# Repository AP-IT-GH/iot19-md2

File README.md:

# Internet of Things - Medical delivery

## Groepsleden

Jarno Cools - Project Manager, Documentating and all-round  
Imad El-Azzouzi - PCB designer, Front-end Programmer and Professional Email Sender to Mr. Luyts         
Oussama Es-Salhi - Back-end Programmer / Systems integrator  
Cristian Baba - Front-end programmer / system testing and programming

## Documentatie

[Medical Delivery Analyse](/doc/analyse.md)

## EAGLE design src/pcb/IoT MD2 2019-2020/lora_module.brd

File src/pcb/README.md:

# PCBs

## MCU module

## LoRa module

## GPS module

## Humidity sensor

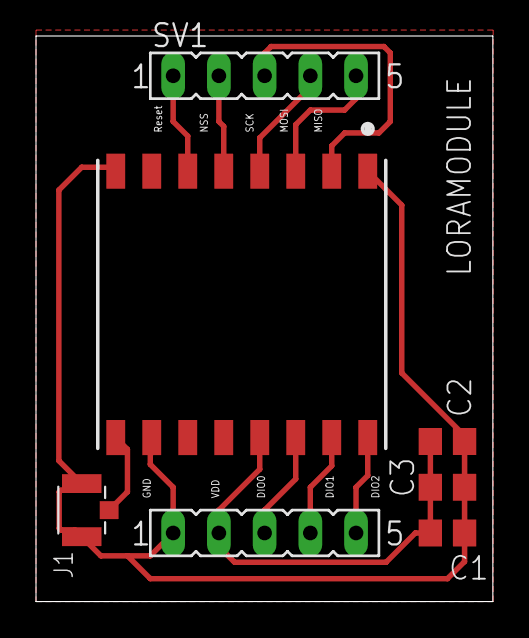
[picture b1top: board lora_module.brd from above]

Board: 2 copper layers, 25.4 x 31.4 mm, 7 parts (0 on the bottom side), 11 nets.

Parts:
C1: 1uF; C0805
C2: 10uF; C0805
C3: 100nF; C0805
J1: U.FL-R-SMT-1(10); HRS_U.FL-R-SMT-1(10)
LORAMODULE: RFM95W-868S2; XCVR_RFM95W-868S2
SV1, SV2: FE05-1

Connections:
DIO0: LORAMODULE.14, SV2.3
DIO1: LORAMODULE.15, SV2.4
DIO2: LORAMODULE.16, SV2.5
GND: C1.2, C2.2, C3.2, J1.1, J1.3, LORAMODULE.1, LORAMODULE.8, LORAMODULE.10, SV2.1
MISO: LORAMODULE.2, SV1.3
MOSI: LORAMODULE.3, SV1.5
unnamed: J1.2, LORAMODULE.9
NSS: LORAMODULE.5, SV1.2
RESET_LORA: LORAMODULE.6, SV1.1
SCK: LORAMODULE.4, SV1.4
VDD: C1.1, C2.1, C3.1, LORAMODULE.13, SV2.2

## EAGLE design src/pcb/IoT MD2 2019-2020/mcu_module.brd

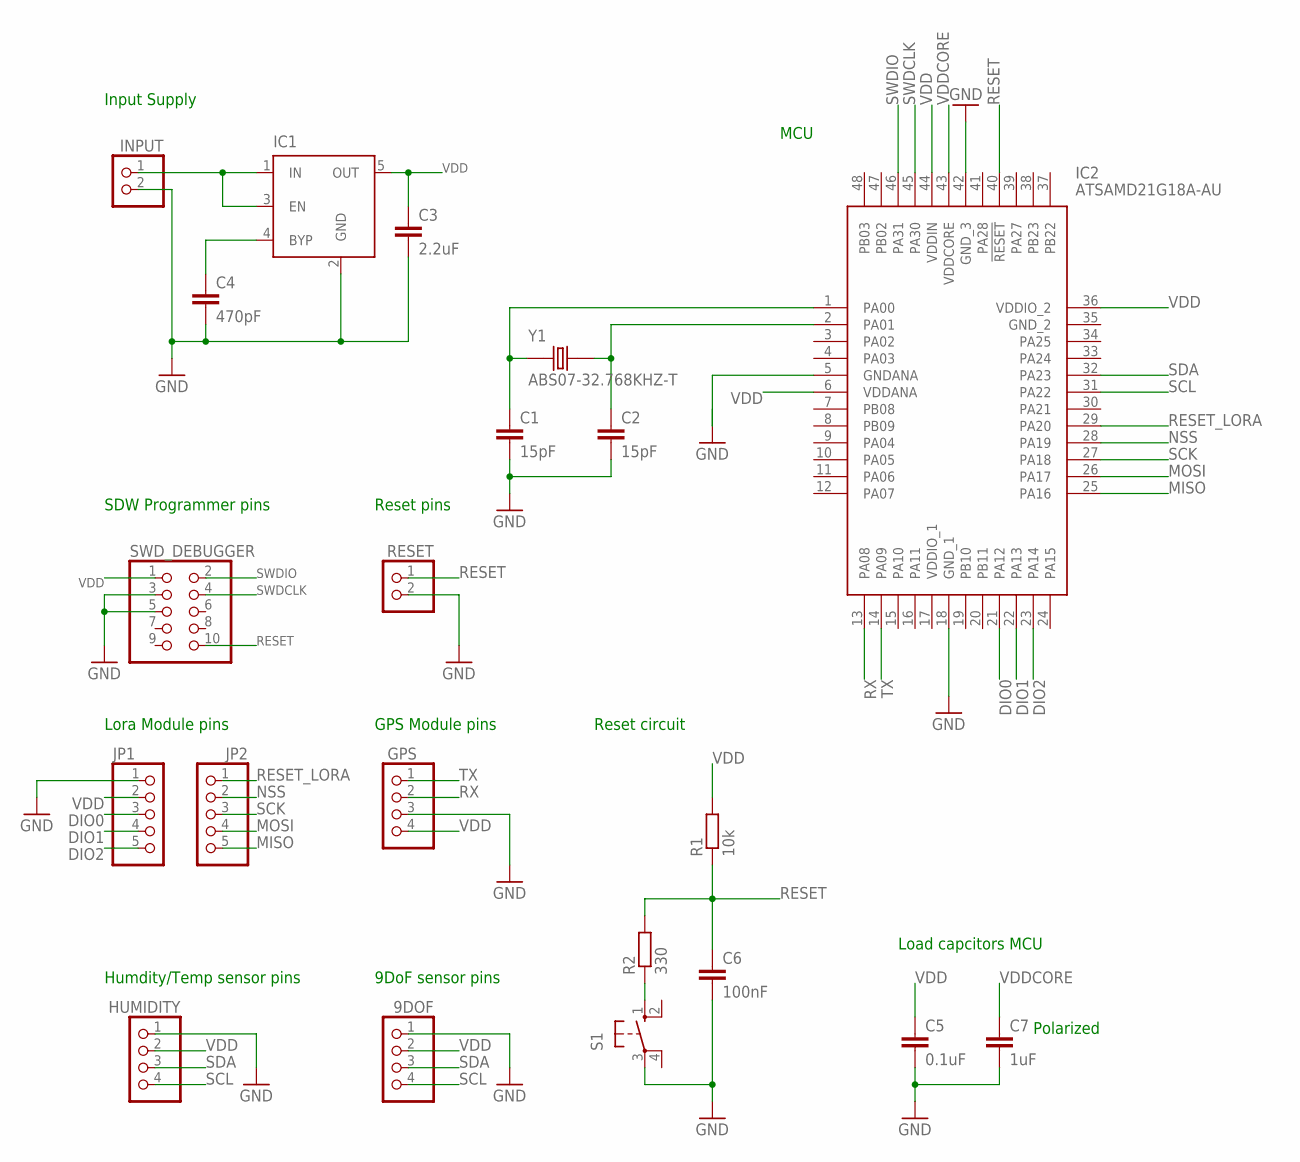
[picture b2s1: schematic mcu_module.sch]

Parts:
9DOF: PINHD-1X4; 1X04
C1, C2: 15pF; C0805
C3: 2.2uF; C0805
C4: 470pF; C0805
C5: 0.1uF; C0805
C6: 100nF; C0805
C7: 1uF; C0805
GPS: PINHD-1X4; 1X04
HUMIDITY: PINHD-1X4; 1X04
IC1: MIC5219XX; SOT23-5
IC2: ATSAMD21G18A-AU; QFP50P900X900X120-48N
INPUT: PINHD-1X2; 1X02
JP1, JP2: PINHD-1X5; 1X05
R1: 10k; R0805
R2: 330; R0805
RESET: PINHD-1X2; 1X02
S1: 10-XX; B3F-10XX
SWD_DEBUGGER: PINHD-2X5; 2X05
Y1: ABS07-32.768KHZ-T; XTAL_ABS07-32.768KHZ-T

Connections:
BYP: C4.1, IC1.4 (BYP)
DIO0: IC2.21 (PA12), JP1.3
DIO1: IC2.22 (PA13), JP1.4
DIO2: IC2.23 (PA14), JP1.5
GND: 9DOF.1, C1.2, C2.2, C3.2, C4.2, C5.2, C6.2, C7.2, GPS.3, HUMIDITY.1, IC1.2 (GND), IC2.5 (GNDANA), IC2.18 (GND_1), IC2.42 (GND_3), INPUT.2, JP1.1, RESET.2, S1.3, SWD_DEBUGGER.3, SWD_DEBUGGER.5
INPUT: IC1.1 (IN), IC1.3 (EN), INPUT.1
MISO: IC2.25 (PA16), JP2.5
MOSI: IC2.26 (PA17), JP2.4
unnamed: C1.1, IC2.1 (PA00), Y1.1
unnamed: C2.1, IC2.2 (PA01), Y1.2
unnamed: R2.1, S1.1 (S)
NSS: IC2.28 (PA19), JP2.2
RESET: C6.1, IC2.40 (!RESET), R1.1, R2.2, RESET.1, SWD_DEBUGGER.10
RESET_LORA: IC2.29 (PA20), JP2.1
RX: GPS.2, IC2.13 (PA08)
SCK: IC2.27 (PA18), JP2.3
SCL: 9DOF.4, HUMIDITY.4, IC2.31 (PA22)
SDA: 9DOF.3, HUMIDITY.3, IC2.32 (PA23)
SWDCLK: IC2.45 (PA30), SWD_DEBUGGER.4
SWDIO: IC2.46 (PA31), SWD_DEBUGGER.2
TX: GPS.1, IC2.14 (PA09)
VDD: 9DOF.2, C3.1, C5.1, GPS.4, HUMIDITY.2, IC1.5 (OUT), IC2.6 (VDDANA), IC2.36 (VDDIO_2), IC2.44 (VDDIN), JP1.2, R1.2, SWD_DEBUGGER.1
VDDCORE: C7.1, IC2.43 (VDDCORE)

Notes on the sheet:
Input Supply
SDW Programmer pins
Reset pins
Lora Module pins
Load capcitors MCU
Reset circuit
GPS Module pins
Humdity/Temp sensor pins
9DoF sensor pins
MCU
Polarized

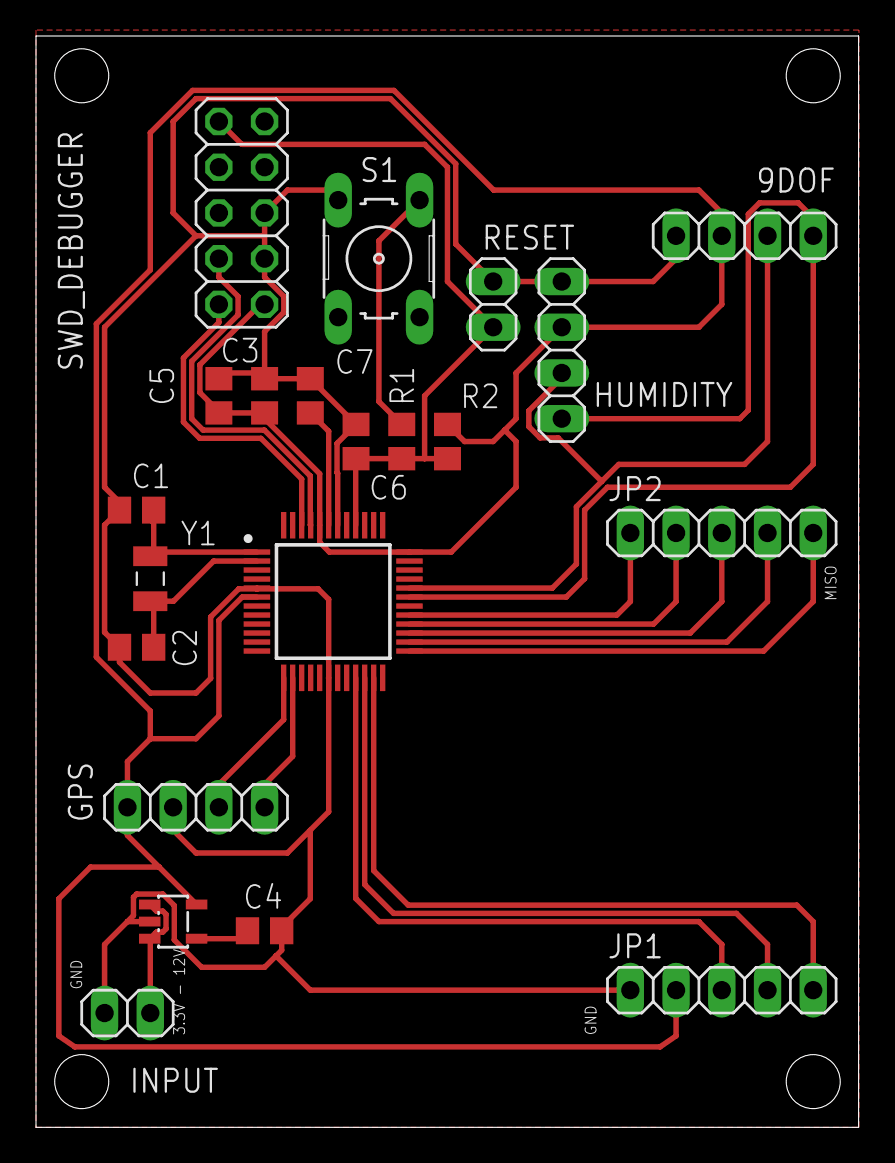
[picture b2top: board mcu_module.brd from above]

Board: 2 copper layers, 45.7 x 60.6 mm, 21 parts (0 on the bottom side), 23 nets.

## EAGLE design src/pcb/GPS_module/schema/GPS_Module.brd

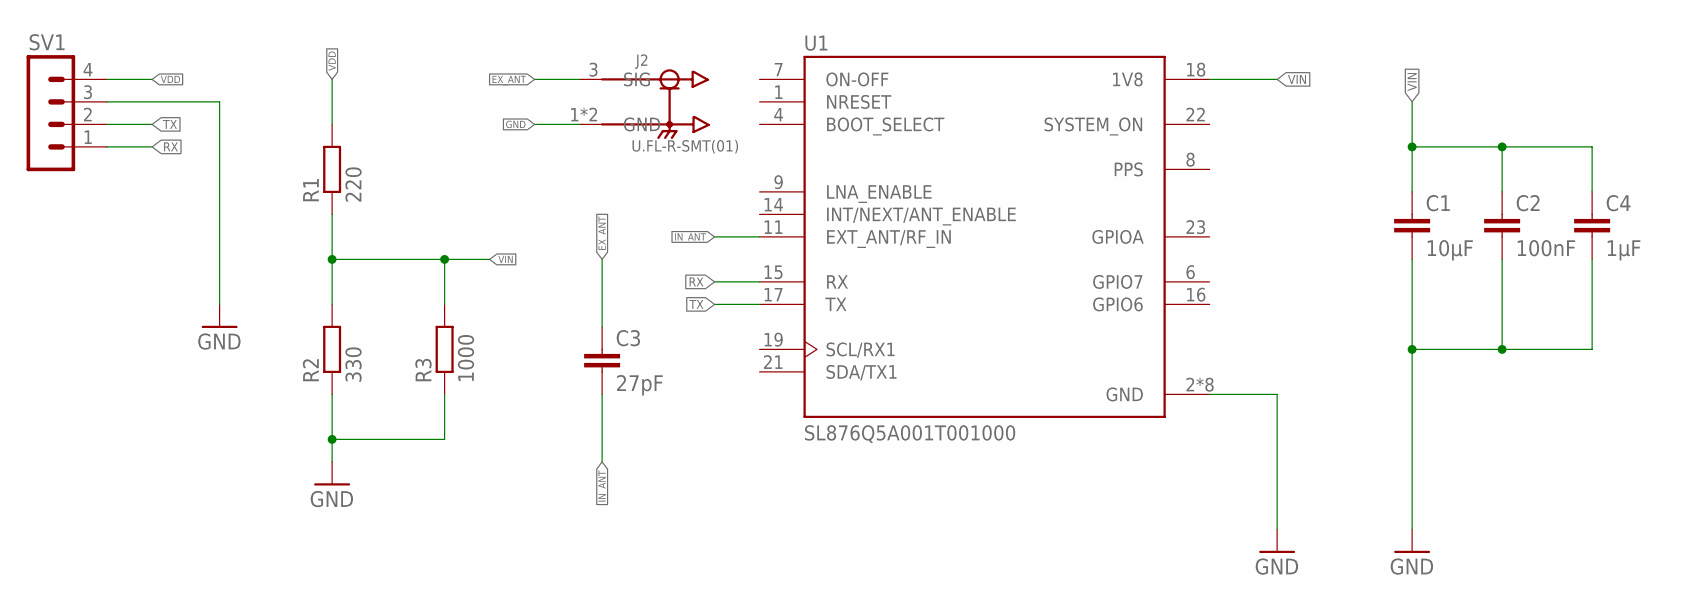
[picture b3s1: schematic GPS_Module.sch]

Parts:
C1: 10µF; C0805
C2: 100nF; C0805
C3: 27pF; C0805
C4: 1µF; C0805
J2: U.FL-R-SMT(01); HRS_U.FL-R-SMT(01)
R1: 220; R0402
R2: 330; R0402
R3: 1000; R0402
SV1: MA04-1
U1: SL876Q5A001T001000; XCVR_SL876Q5A001T001000

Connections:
EX_ANT: C3.1, J2.3 (SIG)
GND: C1.2, C2.2, C4.2, J2.1 (GND), J2.2 (GND), R2.1, R3.1, SV1.3, U1.2 (GND), U1.3 (GND), U1.5 (GND), U1.10 (GND), U1.12 (GND), U1.13 (GND), U1.20 (GND), U1.24 (GND)
IN_ANT: C3.2, U1.11 (EXT_ANT/RF_IN)
RX: SV1.1, U1.15 (RX)
TX: SV1.2, U1.17 (TX)
VDD: R1.2, SV1.4
VIN: C1.1, C2.1, C4.1, R1.1, R2.2, R3.2, U1.18 (1V8)

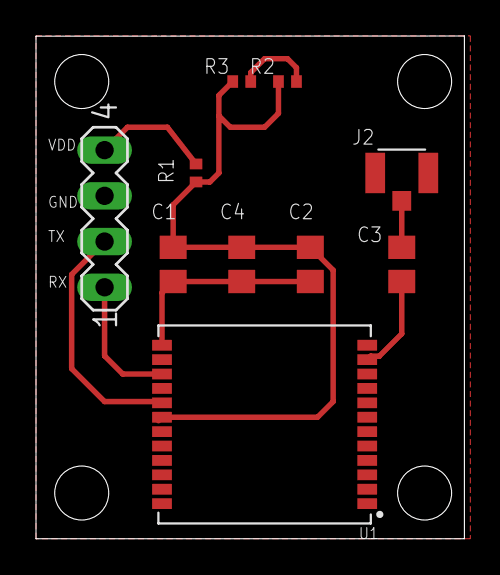
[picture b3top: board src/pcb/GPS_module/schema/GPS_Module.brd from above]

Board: 2 copper layers, 23.8 x 27.9 mm, 10 parts (0 on the bottom side), 7 nets.

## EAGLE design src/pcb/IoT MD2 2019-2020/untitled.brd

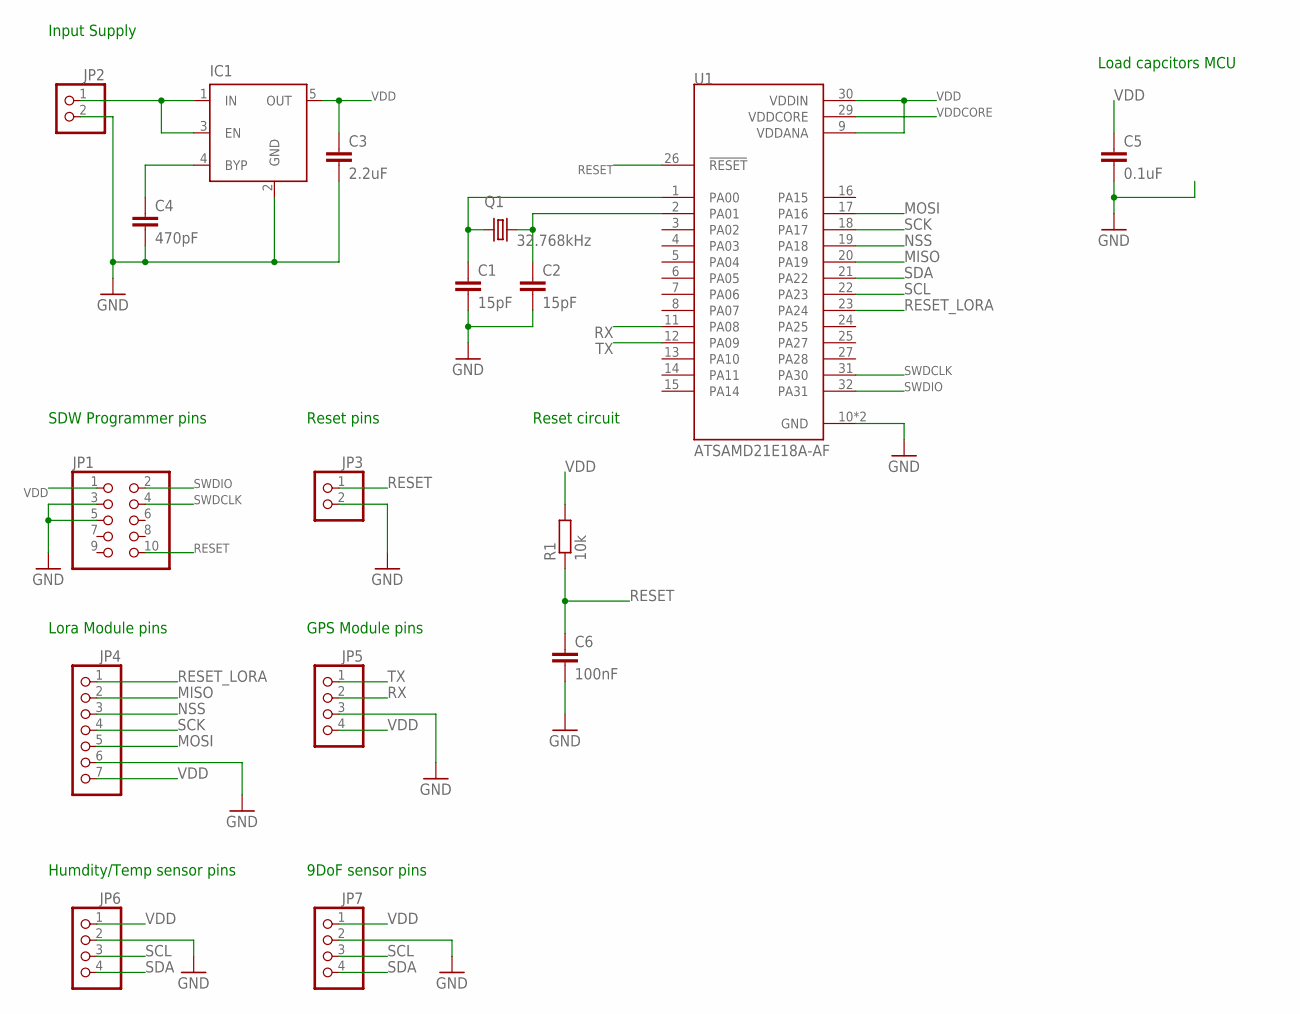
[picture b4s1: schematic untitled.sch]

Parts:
C1, C2: 15pF; C0805
C3: 2.2uF; C0805
C4: 470pF; C0805
C5: 0.1uF; C0805
C6: 100nF; C0805
IC1: MIC5219XX; SOT23-5
JP1: PINHD-2X5; 2X05
JP2, JP3: PINHD-1X2; 1X02
JP4: PINHD-1X7; 1X07
JP5, JP6, JP7: PINHD-1X4; 1X04
Q1: 32.768kHz; CTS406
R1: 10k; R0805
U1: ATSAMD21E18A-AF; QFP80P900X900X120-32N

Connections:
BYP: C4.1, IC1.4 (BYP)
GND: C1.2, C2.2, C3.2, C4.2, C5.2, C6.2, IC1.2 (GND), JP1.3, JP1.5, JP2.2, JP3.2, JP4.6, JP5.3, JP6.2, JP7.2, U1.10 (GND), U1.28 (GND)
INPUT: IC1.1 (IN), IC1.3 (EN), JP2.1
MISO: JP4.2, U1.20 (PA19)
MOSI: JP4.5, U1.17 (PA16)
unnamed: C1.1, Q1.1, U1.1 (PA00)
unnamed: C2.1, Q1.3 (2), U1.2 (PA01)
NSS: JP4.3, U1.19 (PA18)
RESET: C6.1, JP1.10, JP3.1, R1.1, U1.26 (!RESET)
RESET_LORA: JP4.1, U1.23 (PA24)
RX: JP5.2, U1.11 (PA08)
SCK: JP4.4, U1.18 (PA17)
SCL: JP6.3, JP7.3, U1.22 (PA23)
SDA: JP6.4, JP7.4, U1.21 (PA22)
SWDCLK: JP1.4, U1.31 (PA30)
SWDIO: JP1.2, U1.32 (PA31)
TX: JP5.1, U1.12 (PA09)
VDD: C3.1, C5.1, IC1.5 (OUT), JP1.1, JP4.7, JP5.4, JP6.1, JP7.1, R1.2, U1.9 (VDDANA), U1.30 (VDDIN)
VDDCORE: U1.29 (VDDCORE)

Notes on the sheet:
Input Supply
SDW Programmer pins
Reset pins
Lora Module pins
Load capcitors MCU
Reset circuit
GPS Module pins
Humdity/Temp sensor pins
9DoF sensor pins

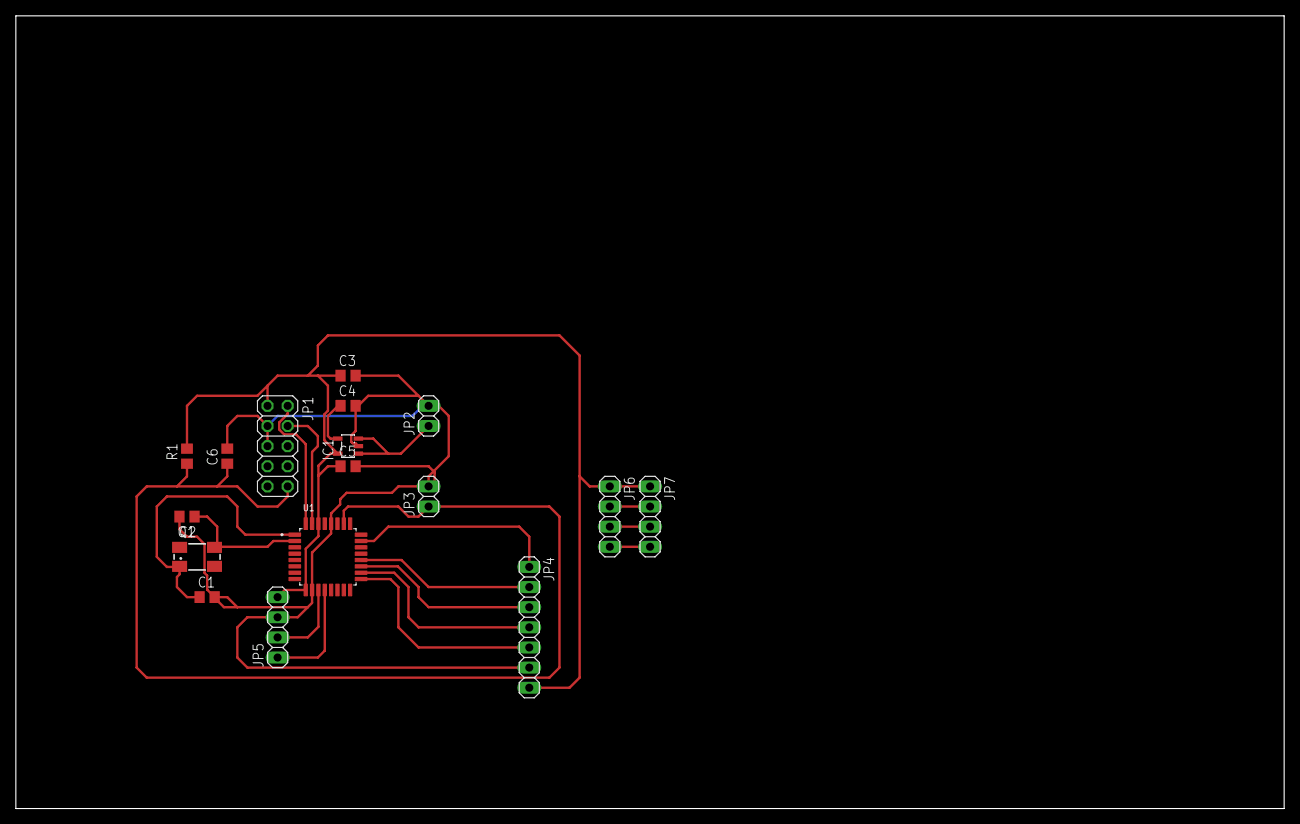
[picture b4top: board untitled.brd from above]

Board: 2 copper layers, 160.0 x 100.0 mm, 17 parts (0 on the bottom side), 18 nets.

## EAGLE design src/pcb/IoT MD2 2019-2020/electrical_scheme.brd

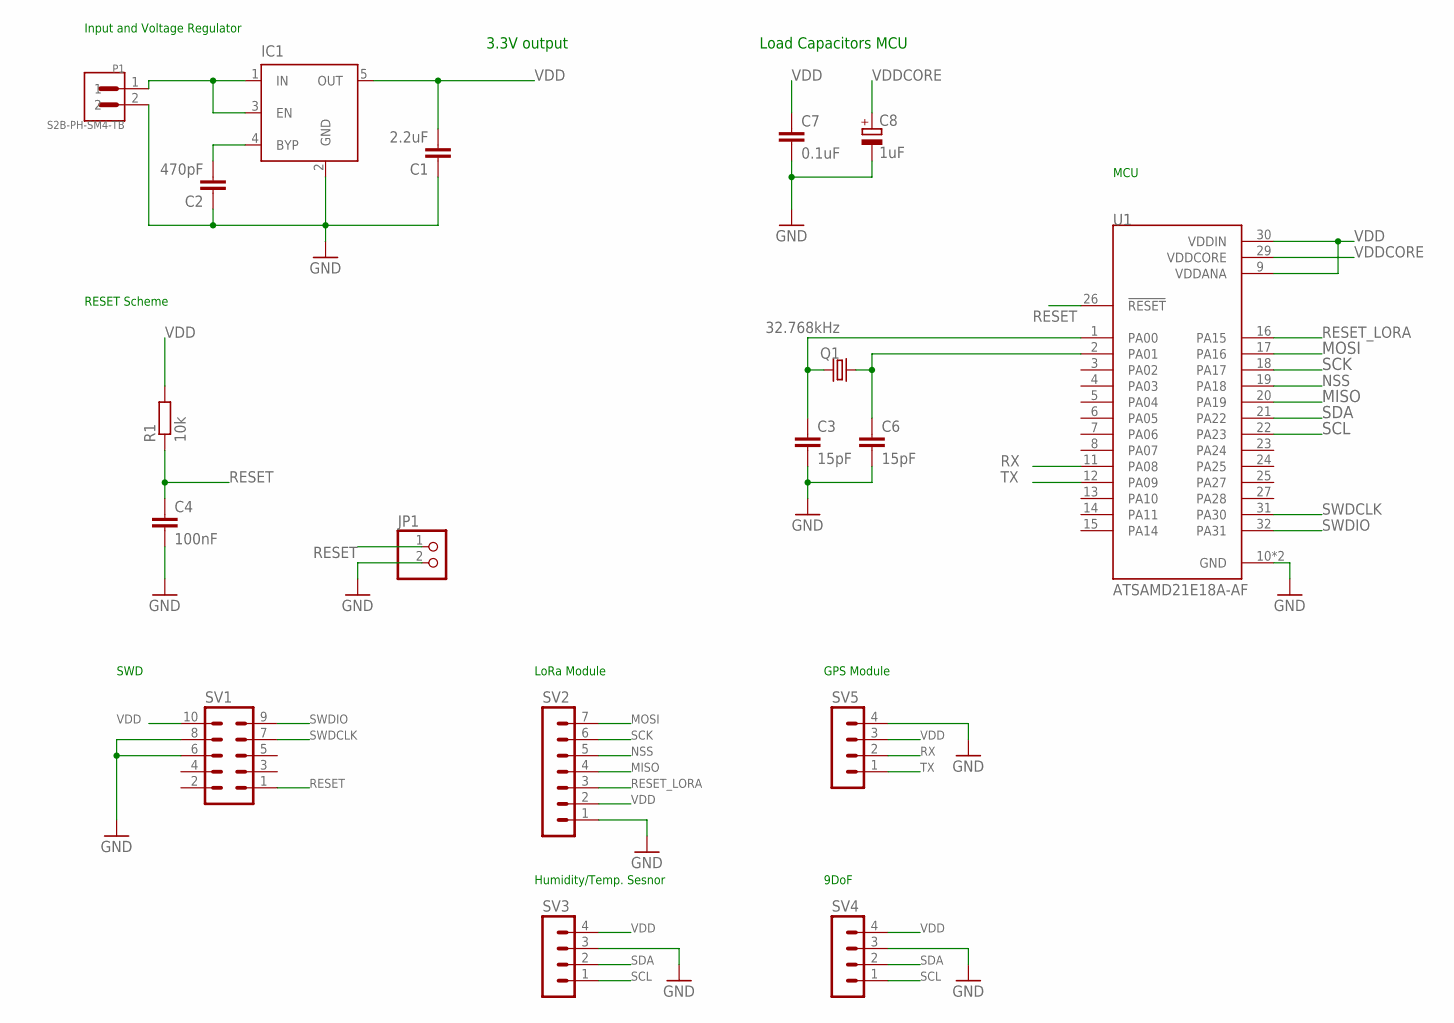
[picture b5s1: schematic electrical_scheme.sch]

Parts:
C1: 2.2uF; C1608
C2: 470pF; C1608
C3, C6: 15pF; C1608
C4: 100nF; C1608
C7: 0.1uF; C1608
C8: 1uF; C/6032-28R
IC1: MIC5219XX; SOT23-5
JP1: PINHD-1X2; 1X02
P1: S2B-PH-SM4-TB; JST_S2B-PH-SM4-TB
Q1: 32.768kHz; MC-306
R1: 10k; R0805
SV1: MA05-2
SV2: MA07-1
SV3, SV4, SV5: MA04-1
U1: ATSAMD21E18A-AF; QFP80P900X900X120-32N

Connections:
GND: C1.1, C2.1, C3.2, C4.2, C6.2, C7.2, C8.-, IC1.2 (GND), JP1.2, P1.2, SV1.6, SV1.8, SV2.1, SV3.3, SV4.3, SV5.4, U1.10 (GND), U1.28 (GND)
MISO: SV2.4, U1.20 (PA19)
MOSI: SV2.7, U1.17 (PA16)
unnamed: C2.2, IC1.4 (BYP)
unnamed: IC1.1 (IN), IC1.3 (EN), P1.1
unnamed: C3.1, Q1.1, U1.1 (PA00)
unnamed: C6.1, Q1.4 (2), U1.2 (PA01)
NSS: SV2.5, U1.19 (PA18)
RESET: C4.1, JP1.1, R1.1, SV1.1, U1.26 (!RESET)
RESET_LORA: SV2.3, U1.16 (PA15)
RX: SV5.2, U1.11 (PA08)
SCK: SV2.6, U1.18 (PA17)
SCL: SV3.1, SV4.1, U1.22 (PA23)
SDA: SV3.2, SV4.2, U1.21 (PA22)
SWDCLK: SV1.7, U1.31 (PA30)
SWDIO: SV1.9, U1.32 (PA31)
TX: SV5.1, U1.12 (PA09)
VDD: C1.2, C7.1, IC1.5 (OUT), R1.2, SV1.10, SV2.2, SV3.4, SV4.4, SV5.3, U1.9 (VDDANA), U1.30 (VDDIN)
VDDCORE: C8.+, U1.29 (VDDCORE)

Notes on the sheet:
3.3V output
SWD
Input and Voltage Regulator
MCU
LoRa Module
Humidity/Temp. Sesnor
9DoF
GPS Module
Load Capacitors MCU
RESET Scheme

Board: 2 copper layers, 18 parts (0 on the bottom side), 19 nets, no tracks yet.

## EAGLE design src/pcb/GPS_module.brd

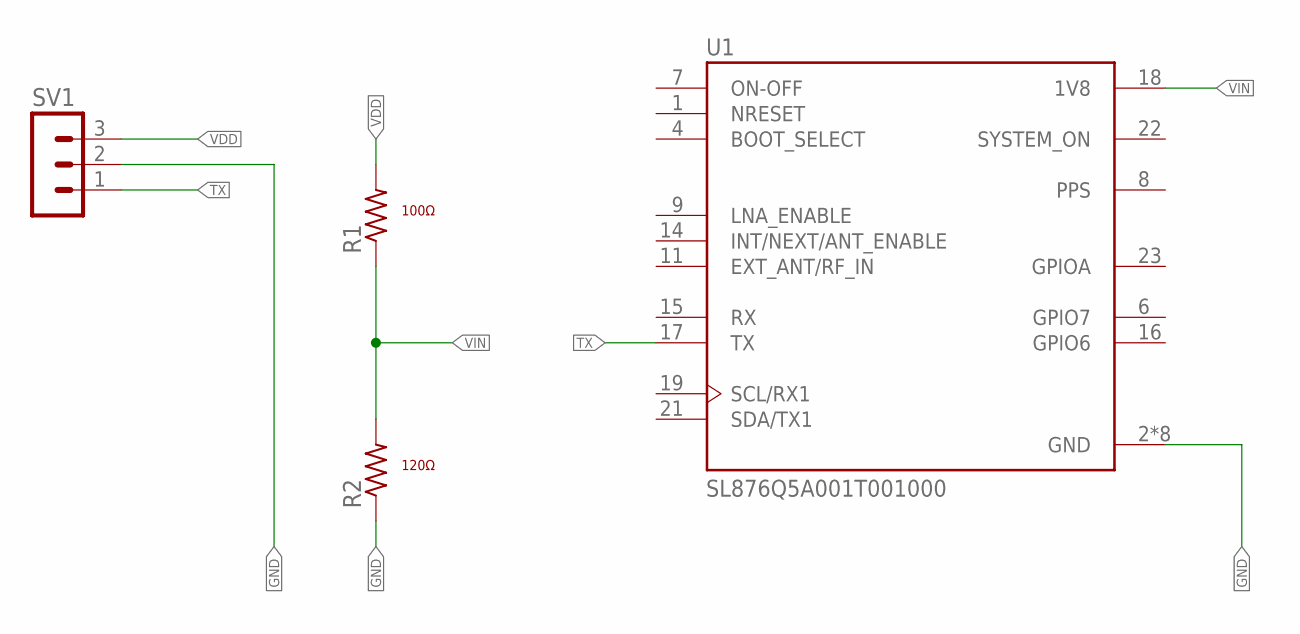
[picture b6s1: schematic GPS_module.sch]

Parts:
R1: 100; RESC2012X65N
R2: 120; RESC2012X65N
SV1: MA03-1
U1: SL876Q5A001T001000; XCVR_SL876Q5A001T001000

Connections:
GND: R2.1, SV1.2, U1.2 (GND), U1.3 (GND), U1.5 (GND), U1.10 (GND), U1.12 (GND), U1.13 (GND), U1.20 (GND), U1.24 (GND)
TX: SV1.1, U1.17 (TX)
VDD: R1.2, SV1.3
VIN: R1.1, R2.2, U1.18 (1V8)

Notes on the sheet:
100Ω
120Ω

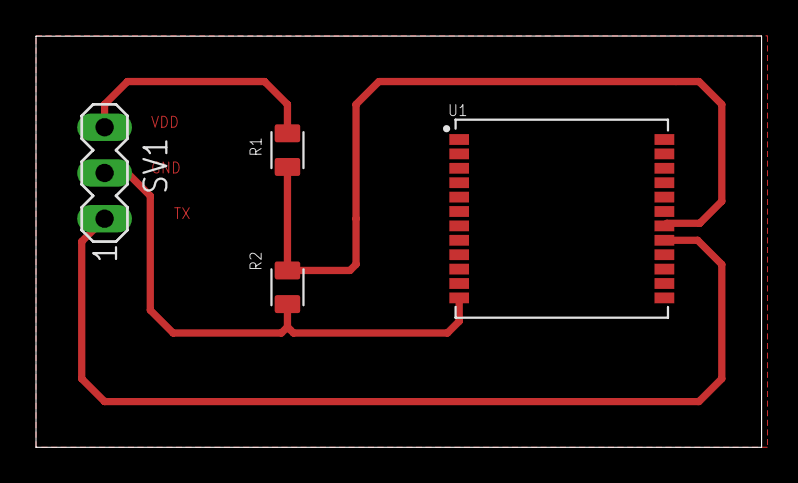
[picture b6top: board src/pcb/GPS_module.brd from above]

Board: 2 copper layers, 40.3 x 22.8 mm, 4 parts (0 on the bottom side), 4 nets.

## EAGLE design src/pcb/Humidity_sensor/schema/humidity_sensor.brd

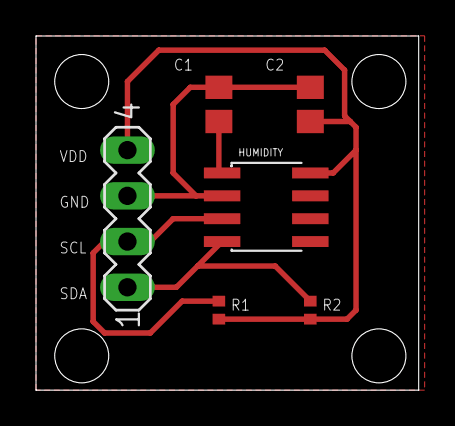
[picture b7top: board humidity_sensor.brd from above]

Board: 2 copper layers, 21.3 x 19.7 mm, 6 parts (0 on the bottom side), 5 nets.

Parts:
C1: 0.1µF; C0805
C2: 0.22µF; C0805
HUMIDITY: HIH6030-021-001
R1, R2: 2.2k; R0402
SV1: MA04-1

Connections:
GND: C1.2, C2.2, HUMIDITY.2, SV1.3
SCL: HUMIDITY.3, R1.1, SV1.2
SDA: HUMIDITY.4, R2.1, SV1.1
VCORE: C1.1, HUMIDITY.1
VDD: C2.1, HUMIDITY.8, R1.2, R2.2, SV1.4

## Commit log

2019-09-18 Added in doc/analyse.md: + Onderzoeksvraag + Overzicht oplossing (dit zonder technische beschrijving)
2019-09-19 Added img fodler in doc and added in image in analyse
2019-09-19 Added Mockup and Blokdiagram specifications a bit
2019-09-20 Added blockscheme image and also added image into analyse.md
2019-09-20 added in block specifications
2019-09-20 added flowchart.png and flowchart image into analyse.md
2019-09-20 added gps electrical specifications
2019-09-21 Changed blockscheme picture
2019-09-21 added gps electrical specs
2019-09-21 Added marktonderzoek
2019-09-21 Marktonderzoek
2019-09-21 specificatietabel aangepast (gps blok)
2019-09-21 gps argumentatie toegevoegd
2019-09-21 analyse marktonderzoek
2019-09-21 Added LoRa module argumentatie
2019-09-21 LMT87 temp sensor electrical specs added
2019-09-21 Added Microcontroller information
2019-09-21 temperatuursensor argumentatie toegevoegd
2019-09-21 Added 9dof
2019-09-21 Added electrical scheme
2019-09-22 Added inventarisaties
2019-09-22 added release plan
2019-09-22 added database model
2019-09-22 Deleted: .vs folder and files inside it, Added: verdediging analyse.pdf
2019-09-22 Modified ppt, added blockscheme software
2019-09-22 backend argumentatie toegevoegd
2019-09-22 Test push for knowing if master is nit pushable without review
2019-09-23 Power consumption
2019-09-23 Added atmel power consumption
2019-09-23 Changed the look of powerconsumption.md
2019-09-26 Template power consumption
2019-09-26 Added countries in marktonderzoek
2019-09-26 Changed release planm
2019-09-26 changed electrical scheme
2019-09-26 Update Power Consumption
2019-09-28 Added datasheet folder + 2 datasheets pdf format. Added electrical_scheme.md and explained the schematic
2019-09-28 flowchart doen
2019-09-28 Added pCB designs gps module, and explanation connections schemes
2019-09-28 Updated datasheet
2019-09-29 argumentatietabel aangepast, totale verbruik berekend
2019-09-30 removed LMT87 from calculation
2019-09-30 bill of materials
2019-09-30 Added footrpints folder, added gps user guide, changed electrical scheme doc for the gps
2019-09-30 Working on 9Dof
2019-09-30 added link to documentation, added link to bill of materials
2019-09-30 Added: Voltage regulator Datasheet Modified: electrical_scheme.pdf -> information about voltage regulate Deleted: Old datasheet voltage regulator
2019-09-30 Added eagle project with electrical scheme
2019-09-30 Changed electrical scheme + image
2019-09-30 Update .md files
2019-09-30 updated pcb scheme, board and img
2019-10-01 Added board, modified scheme grounds for ground plane
2019-10-02 Deleted board + added reset circuit into scheme -> TODO: add smd switch into reset circuit
2019-10-02 updated img
2019-10-02 Added GerberFiles and Automatic_backups
    deleted old img from board, changed lines to pcb, added ground plane
2019-10-02 created GPS_Module map
2019-10-03 Board scheme
2019-10-03 Finished PCB, added gerber files
2019-10-03 Optimized pcb design
2019-10-03 Added electrical_scheme information about pins, added mcu module images.
2019-10-03 Updated voltage regulator in specifaction table
2019-10-03 added humidity sensor scheme, board scheme, images and updated GPS module
2019-10-03 Update README.md
    added right amount of pins
2019-10-04 Added 3d images of pcb
2019-10-04 Added code documentation
2019-10-04 Changed gerber files for export PCB
2019-10-04 updated footprint, humidity sensor pcb, gps module pcb and images, added gerberfiles
2019-10-04 update 9dof
2019-10-04 Added lines to code.md, added sprint_meetings file
2019-10-07 Updated electrical scheme to ATSAMD21G
2019-10-07 Gerber files MCU v2, IMAGES MCU V2 added
2019-10-07 Changed electrical scheme in /doc folder and delted .vs folder
2019-10-07 Updated gerber files
2019-10-07 Modified eagle.epf exported file
2019-10-07 Added scheme lora module
2019-10-07 added foot prints
2019-10-07 added footprints, updated gps scheme by adding antenna pin
2019-10-08 Added gerber files in folder
2019-10-11 Changed 5x2 pinheader LoRa module to 2x 5x1 pinheader
2019-10-11 Added ground to antenna scheme
2019-10-11 Updated GPS Module, Footprints, Automatic backups
2019-10-11 MCU PCB v3
2019-10-11 CAM output files
2019-10-11 9Dof Acc + Gyro ok
2019-10-11 Added 3D m3
2019-10-11 Updated images
2019-10-11 Gerber files
2019-10-11 Added images
2019-10-11 Updated 3d image
2019-10-11 Added bom file
2019-10-11 Added templates
2019-10-11 Added MCU and LoRa module PCB's components in BOM
2019-10-11 bom gps and humidity
2019-10-11 updated bom file
2019-10-12 Changed the LoRa module layout for the connection with the mcu
2019-10-12 Updated PCB Image
2019-10-12 Updated pins for LoRa module
2019-10-12 Added arduino code for transmitting a message over Lora TTN
2019-10-12 added lora antenna doc, mcu-lora code doc
2019-10-14 added presentation pdf
2019-10-18 9dof final update
2019-10-18 Updated images, better quality
2019-10-25 added gps arduino code, added gps output
2019-10-25 added libraries
2019-10-25 updated shematic of GPS and Humidity
2019-10-25 updated read.me
2019-11-04 Added documentation and image graph
2019-11-04 Init Angular project
2019-11-07 Added presentation 3
2019-11-08 angular first commit
2019-11-08 Updated text for pcb
2019-11-22 added add page
2019-11-25 firebase added
2019-11-27 Map working with arr of points
2019-11-29 Maps Working with polyline and marker
2019-11-30 Added testplan
2019-12-02 Small error fixed
2019-12-02 update function
2019-12-05 Dialog working
2019-12-06 update dashboard
2019-12-06 can add a delivery, updated html and css of homepage
2019-12-06 added card, updated html, css
2019-12-07 updated electrical scheme connections
2019-12-07 Added humidity test and README.md in test folder
2019-12-07 added humidity datasheet
2019-12-08 can add box to a delivery
2019-12-08 updated html and css
2019-12-08 Added Lasercut files and gerber outputs, also updates from mcu and lora module (jlcpcb modifications)
2019-12-08 updated design
2019-12-08 added mqtt backend
2019-12-09 packagejson-log fix
2019-12-09 Added gps and mcu test
2019-12-12 Added img Xplained_Pro_Pinout, added tests/lora, Updated elechtrical scheme
2019-12-12 Added SPI test
2019-12-12 can add boxes to delivery
2019-12-13 Added SPItest2
2019-12-14 Added lora test 3
2019-12-14 Added library, screenshots library.
2019-12-16 added information
2019-12-16 Updated lora scheme
2019-12-18 Added information about pinmappig
2019-12-18 added interfaces
2019-12-18 Made object in object an array
2019-12-18 Working array
2019-12-18 fix small errors, can get realtime data of box, updated info page
2019-12-27 Added integration
2020-01-07 add or delete transporter, add box to a transporter or delete box
2020-01-07 added gps, humidity, lora integration code
2020-01-07 added final presentation
